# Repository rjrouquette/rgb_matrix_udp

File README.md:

# RGB Matrix Panel Driver using Raspberry Pi
Uses UDP protocol and a custom adapter board to drive RGB Panels.

The custom driver board eliminates flickering under high CPU load by utilizing the DPI interface to generate the output signals independent of the CPU.  This prevents heavy CPU load and interrupts from causing the panel brightness to flicker.  The DPI interfaces provides a 24-bit parallel interface with pixel clock, HSYNC, and VSYNC signals.  The 24-bit width allows for driving 4 chains of LED panels.

The UDP server and clients synchornize multiple Raspberry Pis to support both larger aggregate arrays and duplication of video feeds.  The server and clients must be synchronized to the same master clock using either chrony or ntpd.

This project references https://github.com/hzeller/rpi-rgb-led-matrix

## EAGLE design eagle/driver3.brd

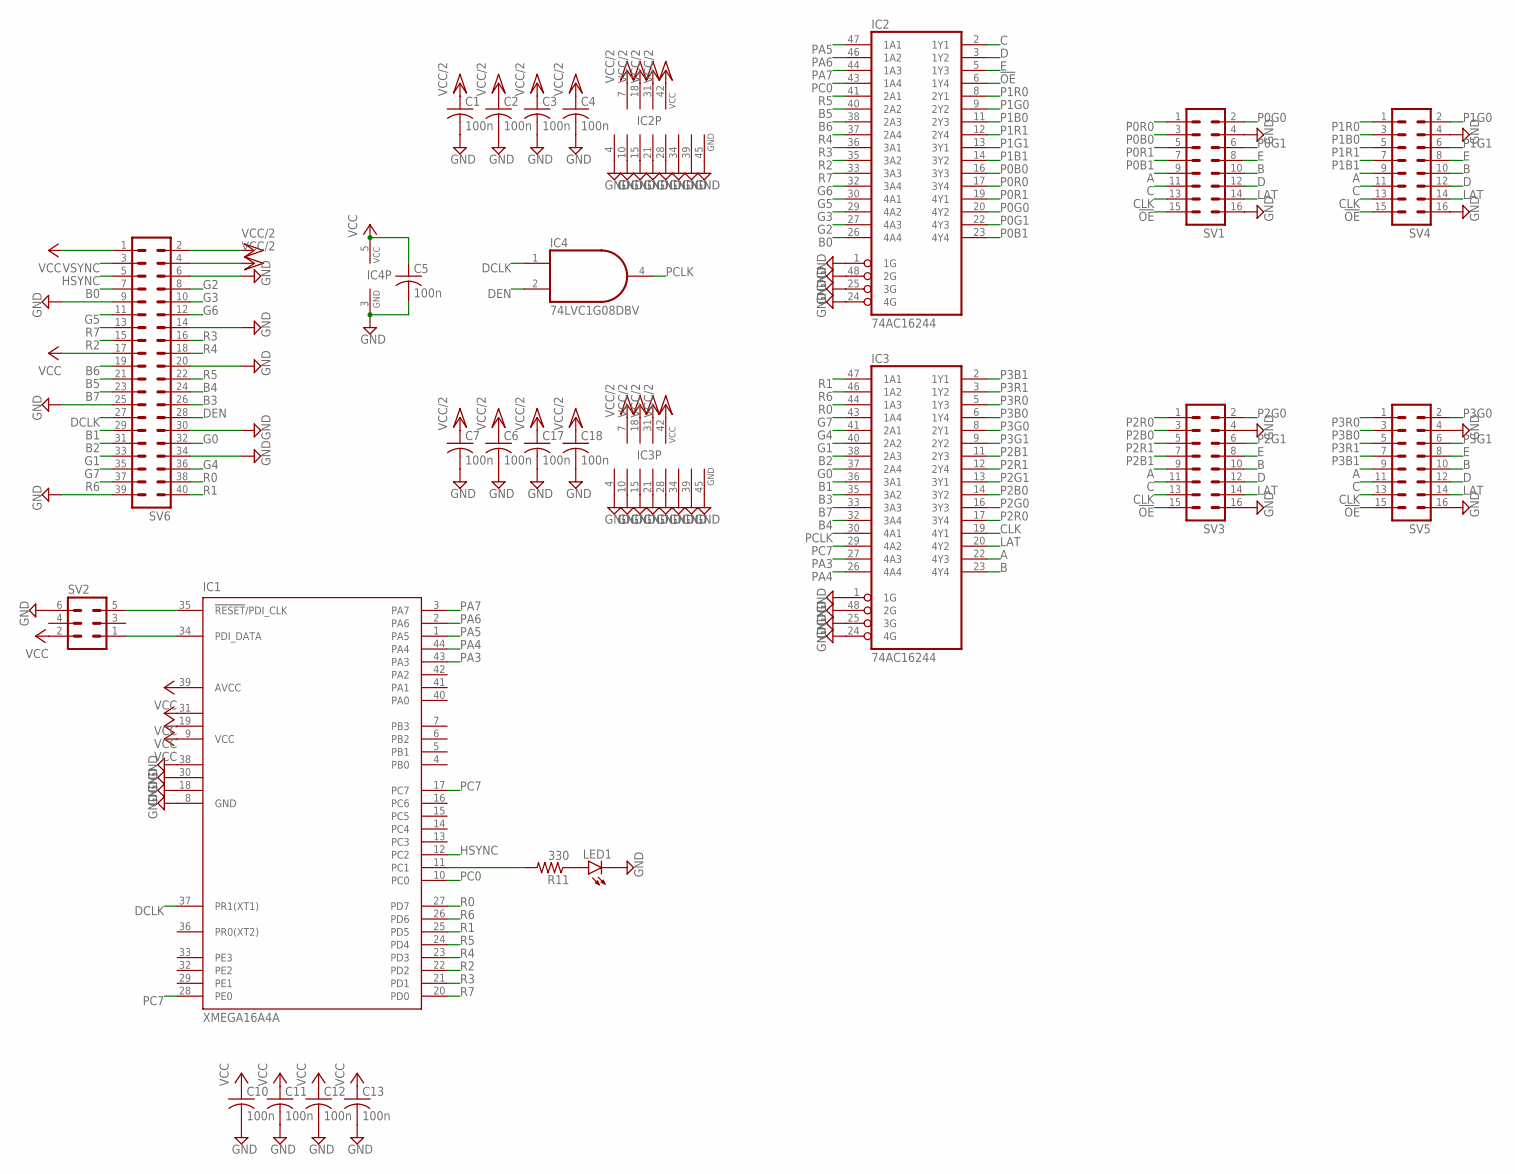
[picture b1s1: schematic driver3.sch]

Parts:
C1, C2, C3, C4, C5, C6, C7, C10, C11, C12, C13, C17, C18: 100n; C0402
IC1: XMEGA16A4A; TQFP44
IC2, IC3: 74AC16244; SSOP48DL
IC4: 74LVC1G08DBV; SOT23-5
LED1: LEDCHIPLED_0805; CHIPLED_0805
R11: 330; R0402
SV1, SV3, SV4, SV5: MA08-2
SV2: MA03-2
SV6: MA20-2

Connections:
!OE: IC2.6 (1Y4), SV1.15, SV3.15, SV4.15, SV5.15
A: IC3.22 (4Y3), SV1.9, SV3.9, SV4.9, SV5.9
B: IC3.23 (4Y4), SV1.10, SV3.10, SV4.10, SV5.10
B0: IC2.26 (4A4), SV6.7
B1: IC3.36 (3A1), SV6.29
B2: IC3.38 (2A3), SV6.31
B3: IC3.35 (3A2), SV6.26
B4: IC3.32 (3A4), SV6.24
B5: IC2.40 (2A2), SV6.21
B6: IC2.38 (2A3), SV6.19
B7: IC3.33 (3A3), SV6.23
C: IC2.2 (1Y1), SV1.11, SV3.11, SV4.11, SV5.11
CLK: IC3.19 (4Y1), SV1.13, SV3.13, SV4.13, SV5.13
D: IC2.3 (1Y2), SV1.12, SV3.12, SV4.12, SV5.12
DCLK: IC1.37 (PR1(XT1)), IC4.1 (I0), SV6.27
DEN: IC4.2 (I1), SV6.28
E: IC2.5 (1Y3), SV1.8, SV3.8, SV4.8, SV5.8
G0: IC3.37 (2A4), SV6.32
G1: IC3.40 (2A2), SV6.33
G2: IC2.27 (4A3), SV6.8
G3: IC2.29 (4A2), SV6.10
G4: IC3.41 (2A1), SV6.36
G5: IC2.30 (4A1), SV6.11
G6: IC2.32 (3A4), SV6.12
G7: IC3.43 (1A4), SV6.35
GND: C1.2, C2.2, C3.2, C4.2, C5.2, C6.2, C7.2, C10.2, C11.2, C12.2, C13.2, C17.2, C18.2, IC1.8 (GND), IC1.18 (GND1), IC1.30 (GND2), IC1.38 (GND3), IC2.1 (1G), IC2.4 (GND), IC2.10 (GND), IC2.15 (GND), IC2.21 (GND), IC2.24 (4G), IC2.25 (3G), IC2.28 (GND), IC2.34 (GND), IC2.39 (GND), IC2.45 (GND), IC2.48 (2G), IC3.1 (1G), IC3.4 (GND), IC3.10 (GND), IC3.15 (GND), IC3.21 (GND), IC3.24 (4G), IC3.25 (3G), IC3.28 (GND), IC3.34 (GND), IC3.39 (GND), IC3.45 (GND), IC3.48 (2G), IC4.3 (GND), LED1.C, SV1.4, SV1.16, SV2.6, SV3.4, SV3.16, SV4.4, SV4.16, SV5.4, SV5.16, SV6.6, SV6.9, SV6.14, SV6.20, SV6.25, SV6.30, SV6.34, SV6.39
HSYNC: IC1.12 (PC2), SV6.5
LAT: IC3.20 (4Y2), SV1.14, SV3.14, SV4.14, SV5.14
unnamed: IC1.11 (PC1), R11.2
unnamed: IC1.34 (PDI_DATA), SV2.1
unnamed: IC1.35 (!RESET!/PDI_CLK), SV2.5
unnamed: LED1.A, R11.1
P0B0: IC2.16 (3Y3), SV1.3
P0B1: IC2.23 (4Y4), SV1.7
P0G0: IC2.20 (4Y2), SV1.2
P0G1: IC2.22 (4Y3), SV1.6
P0R0: IC2.17 (3Y4), SV1.1
P0R1: IC2.19 (4Y1), SV1.5
P1B0: IC2.11 (2Y3), SV4.3
P1B1: IC2.14 (3Y2), SV4.7
P1G0: IC2.9 (2Y2), SV4.2
P1G1: IC2.13 (3Y1), SV4.6
P1R0: IC2.8 (2Y1), SV4.1
P1R1: IC2.12 (2Y4), SV4.5
P2B0: IC3.14 (3Y2), SV3.3
P2B1: IC3.11 (2Y3), SV3.7
P2G0: IC3.16 (3Y3), SV3.2
P2G1: IC3.13 (3Y1), SV3.6
P2R0: IC3.17 (3Y4), SV3.1
P2R1: IC3.12 (2Y4), SV3.5
P3B0: IC3.6 (1Y4), SV5.3
P3B1: IC3.2 (1Y1), SV5.7
P3G0: IC3.8 (2Y1), SV5.2
P3G1: IC3.9 (2Y2), SV5.6
P3R0: IC3.5 (1Y3), SV5.1
P3R1: IC3.3 (1Y2), SV5.5
PA3: IC1.43 (PA3), IC3.27 (4A3)
PA4: IC1.44 (PA4), IC3.26 (4A4)
PA5: IC1.1 (PA5), IC2.47 (1A1)
PA6: IC1.2 (PA6), IC2.46 (1A2)
PA7: IC1.3 (PA7), IC2.44 (1A3)
PC0: IC1.10 (PC0), IC2.43 (1A4)
PC7: IC1.17 (PC7), IC1.28 (PE0), IC3.29 (4A2)
PCLK: IC3.30 (4A1), IC4.4 (O)
R0: IC1.27 (PD7), IC3.44 (1A3), SV6.38
R1: IC1.25 (PD5), IC3.47 (1A1), SV6.40
R2: IC1.22 (PD2), IC2.35 (3A2), SV6.15
R3: IC1.21 (PD1), IC2.36 (3A1), SV6.16
R4: IC1.23 (PD3), IC2.37 (2A4), SV6.18
R5: IC1.24 (PD4), IC2.41 (2A1), SV6.22
R6: IC1.26 (PD6), IC3.46 (1A2), SV6.37
R7: IC1.20 (PD0), IC2.33 (3A3), SV6.13
VCC: C5.1, C10.1, C11.1, C12.1, C13.1, IC1.9 (VCC), IC1.19 (VCC1), IC1.31 (VCC2), IC1.39 (AVCC), IC4.5 (VCC), SV2.2, SV6.1, SV6.17
VCC/2: C1.1, C2.1, C3.1, C4.1, C6.1, C7.1, C17.1, C18.1, IC2.7 (VCC), IC2.18 (VCC), IC2.31 (VCC), IC2.42 (VCC), IC3.7 (VCC), IC3.18 (VCC), IC3.31 (VCC), IC3.42 (VCC), SV6.2, SV6.4
VSYNC: SV6.3

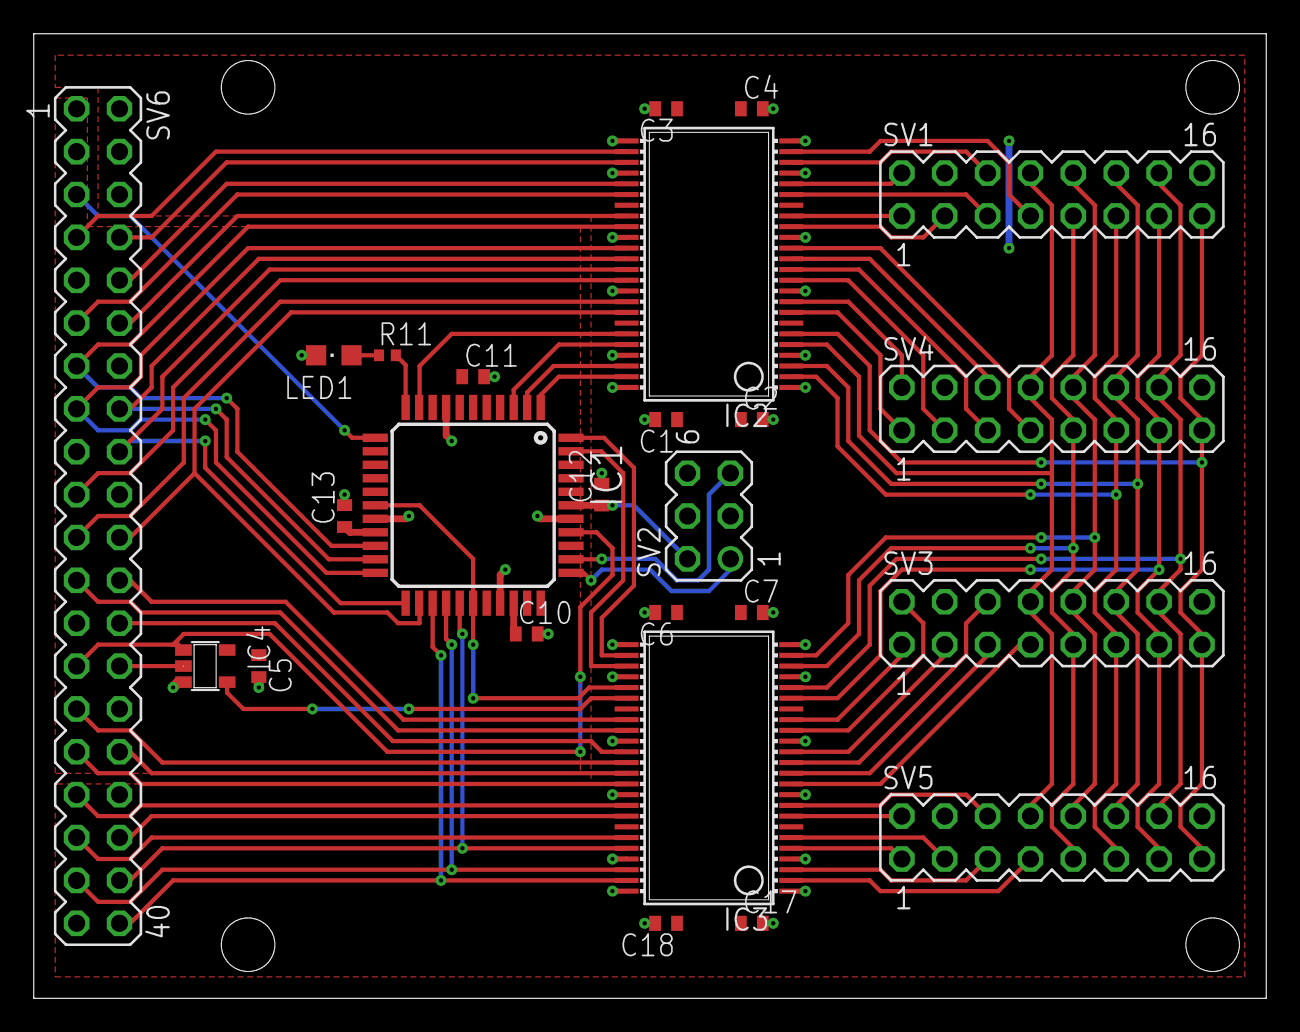
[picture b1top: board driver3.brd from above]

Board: 2 copper layers, 73.0 x 57.1 mm, 25 parts (0 on the bottom side), 74 nets.

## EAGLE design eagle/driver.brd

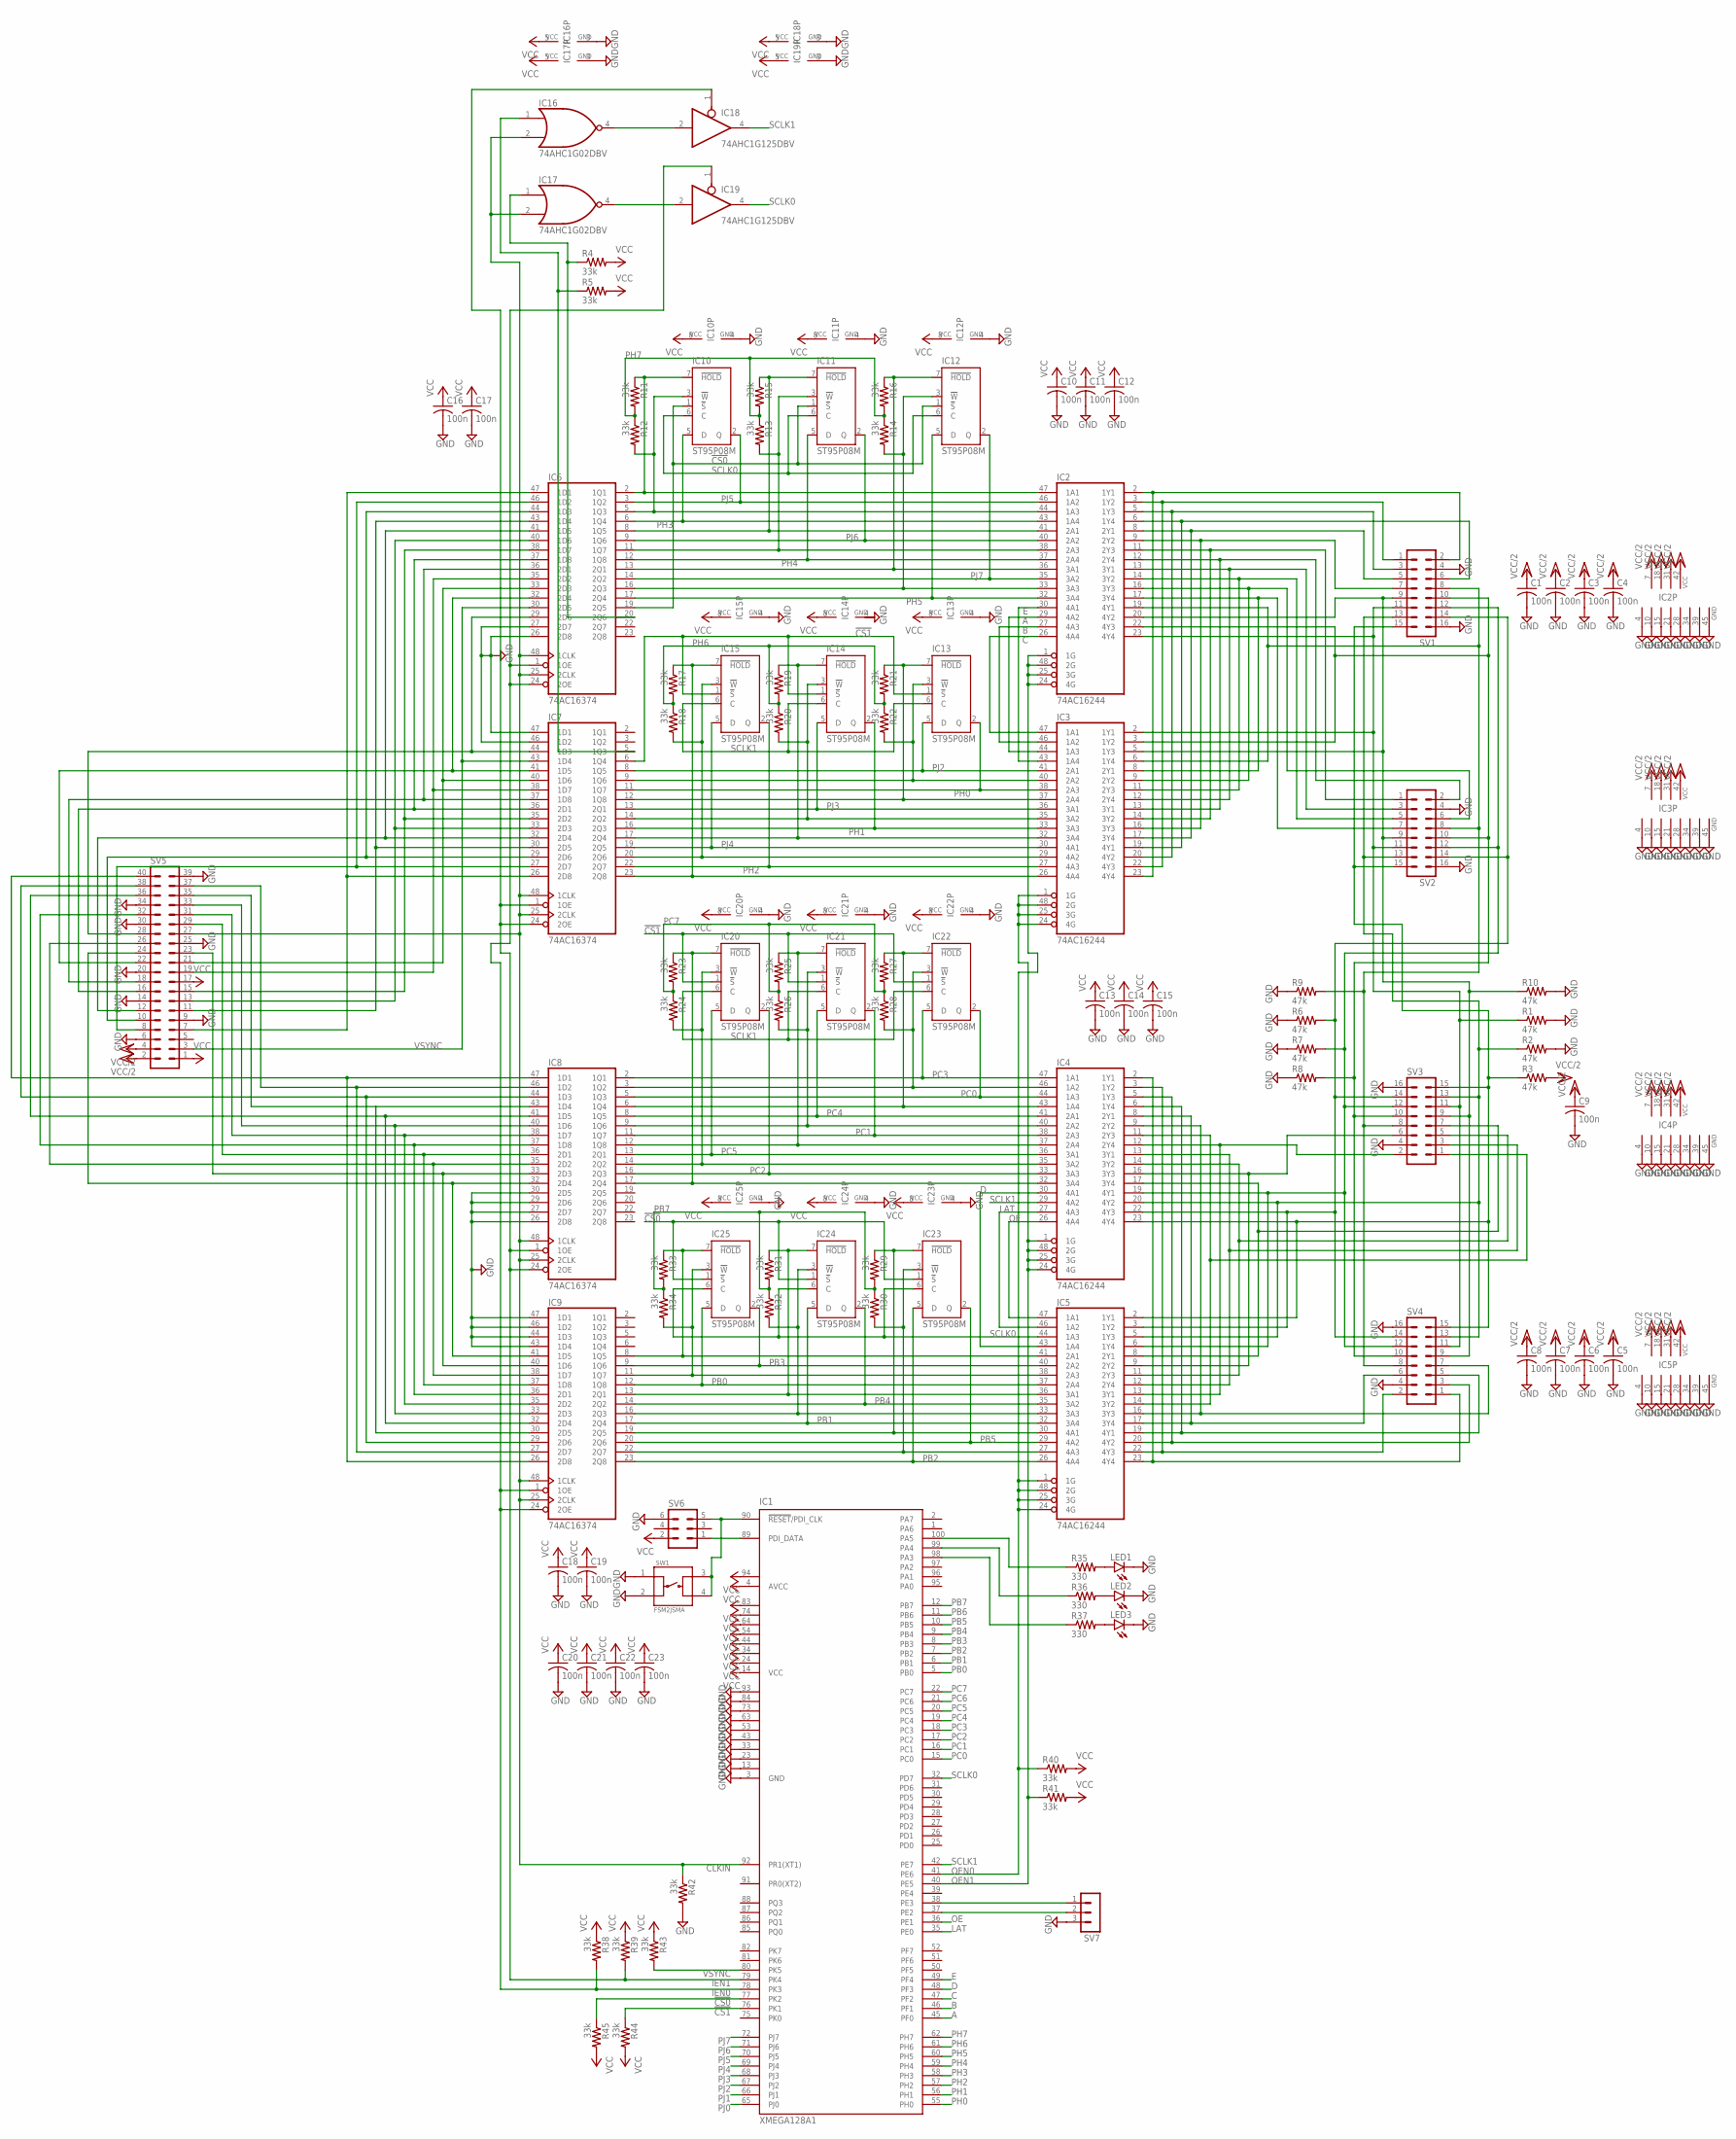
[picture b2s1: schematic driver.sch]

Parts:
C1, C2, C3, C4, C5, C6, C7, C8, C9, C10, C11, C12, C13, C14, C15, C16, C17, C18, C19, C20, C21, C22, C23: 100n; C0402
IC1: XMEGA128A1; TQFP100
IC2, IC3, IC4, IC5: 74AC16244; SSOP48DL
IC6, IC7, IC8, IC9: 74AC16374; SSOP48DL
IC10, IC11, IC12, IC13, IC14, IC15, IC20, IC21, IC22, IC23, IC24, IC25: ST95P08M; SO08
IC16, IC17: 74AHC1G02DBV; SOT23-5
IC18, IC19: 74AHC1G125DBV; SOT23-5
LED1, LED2, LED3: LEDCHIPLED_0805; CHIPLED_0805
R1, R2, R3, R6, R7, R8, R9, R10: 47k; R0402
R4, R5, R11, R12, R13, R14, R15, R16, R17, R18, R19, R20, R21, R22, R23, R24, R25, R26, R27, R28, R29, R30, R31, R32, R33, R34, R38, R39, R40, R41, R42, R43, R44, R45: 33k; R0402
R35, R36, R37: 330; R0402
SV1, SV2, SV3, SV4: MA08-2
SV5: MA20-2
SV6: MA03-2
SV7: MA03-1
SW1: FSM2JSMA

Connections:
!CS0: IC1.77 (PK2), IC6.19 (2Q5), IC10.1 (!S), IC11.1 (!S), IC12.1 (!S), IC23.1 (!S), IC24.1 (!S), IC25.1 (!S), R45.1
!CS1: IC1.76 (PK1), IC7.6 (1Q4), IC13.1 (!S), IC14.1 (!S), IC15.1 (!S), IC20.1 (!S), IC21.1 (!S), IC22.1 (!S), R44.1
A: IC1.45 (PF0), IC2.29 (4A2), IC3.44 (1A3)
B: IC1.46 (PF1), IC2.27 (4A3), IC3.46 (1A2)
C: IC1.47 (PF2), IC2.26 (4A4), IC3.47 (1A1)
CLKIN: IC1.92 (PR1(XT1)), IC6.25 (2CLK), IC6.48 (1CLK), IC7.25 (2CLK), IC7.48 (1CLK), IC8.25 (2CLK), IC8.48 (1CLK), IC9.25 (2CLK), IC9.48 (1CLK), IC16.2 (I1), IC17.2 (I1), R42.1, SV5.27
D: IC1.48 (PF3), IC4.30 (4A1), IC5.43 (1A4)
E: IC1.49 (PF4), IC2.30 (4A1), IC3.43 (1A4)
GND: C1.2, C2.2, C3.2, C4.2, C5.2, C6.2, C7.2, C8.2, C9.2, C10.2, C11.2, C12.2, C13.2, C14.2, C15.2, C16.2, C17.2, C18.2, C19.2, C20.2, C21.2, C22.2, C23.2, IC1.3 (GND), IC1.13 (GND1), IC1.23 (GND2), IC1.33 (GND3), IC1.43 (GND4), IC1.53 (GND5), IC1.63 (GND6), IC1.73 (GND7), IC1.84 (GND8), IC1.93 (GND9), IC2.4 (GND), IC2.10 (GND), IC2.15 (GND), IC2.21 (GND), IC2.28 (GND), IC2.34 (GND), IC2.39 (GND), IC2.45 (GND), IC3.4 (GND), IC3.10 (GND), IC3.15 (GND), IC3.21 (GND), IC3.28 (GND), IC3.34 (GND), IC3.39 (GND), IC3.45 (GND), IC4.4 (GND), IC4.10 (GND), IC4.15 (GND), IC4.21 (GND), IC4.28 (GND), IC4.34 (GND), IC4.39 (GND), IC4.45 (GND), IC5.4 (GND), IC5.10 (GND), IC5.15 (GND), IC5.21 (GND), IC5.28 (GND), IC5.34 (GND), IC5.39 (GND), IC5.45 (GND), IC6.4 (GND), IC6.10 (GND), IC6.15 (GND), IC6.21 (GND), IC6.26 (2D8), IC6.27 (2D7), IC6.28 (GND), IC6.34 (GND), IC6.39 (GND), IC6.45 (GND), IC7.4 (GND), IC7.10 (GND), IC7.15 (GND), IC7.21 (GND), IC7.28 (GND), IC7.34 (GND), IC7.39 (GND), IC7.45 (GND), IC7.46 (1D2), IC7.47 (1D1), IC8.4 (GND), IC8.10 (GND), IC8.15 (GND), IC8.21 (GND), IC8.26 (2D8), IC8.27 (2D7), IC8.28 (GND), IC8.29 (2D6), IC8.30 (2D5), IC8.34 (GND), IC8.39 (GND), IC8.45 (GND), IC9.4 (GND), IC9.10 (GND), IC9.15 (GND), IC9.21 (GND), IC9.28 (GND), IC9.34 (GND), IC9.39 (GND), IC9.43 (1D4), IC9.44 (1D3), IC9.45 (GND), IC9.46 (1D2), IC9.47 (1D1), IC10.4 (GND), IC11.4 (GND), IC12.4 (GND), IC13.4 (GND), IC14.4 (GND), IC15.4 (GND), IC16.3 (GND), IC17.3 (GND), IC18.3 (GND), IC19.3 (GND), IC20.4 (GND), IC21.4 (GND), IC22.4 (GND)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
IEN0: IC1.78 (PK3), IC6.1 (1OE), IC6.24 (2OE), IC9.1 (1OE), IC9.24 (2OE), IC19.1 (OE), R38.2
IEN1: IC1.79 (PK4), IC7.1 (1OE), IC7.24 (2OE), IC8.1 (1OE), IC8.24 (2OE), IC18.1 (OE), R39.2
LAT: IC1.35 (PE0), IC4.27 (4A3), IC5.46 (1A2)
unnamed: IC2.2 (1Y1), IC3.23 (4Y4), SV1.2
unnamed: IC2.3 (1Y2), IC3.22 (4Y3), SV1.1
unnamed: IC2.6 (1Y4), IC3.19 (4Y1), SV1.6
unnamed: IC2.5 (1Y3), IC3.20 (4Y2), SV1.3
unnamed: IC2.8 (2Y1), IC3.17 (3Y4), SV1.5
unnamed: IC2.9 (2Y2), IC3.16 (3Y3), SV1.7
unnamed: IC2.12 (2Y4), IC3.13 (3Y1), SV2.2
unnamed: IC2.14 (3Y2), IC3.11 (2Y3), SV2.5
unnamed: IC2.13 (3Y1), IC3.12 (2Y4), SV2.3
unnamed: IC2.16 (3Y3), IC3.9 (2Y2), SV2.6
unnamed: IC2.19 (4Y1), IC3.6 (1Y4), R9.2, SV1.8, SV2.8, SV3.8, SV4.8
unnamed: IC2.20 (4Y2), IC3.5 (1Y3), R10.1, SV1.9, SV2.9, SV3.9, SV4.9
unnamed: IC2.11 (2Y3), IC3.14 (3Y2), SV2.1
unnamed: IC2.23 (4Y4), IC3.2 (1Y1), R1.1, SV1.11, SV2.11, SV3.11, SV4.11
unnamed: IC2.22 (4Y3), IC3.3 (1Y2), R8.2, SV1.10, SV2.10, SV3.10, SV4.10
unnamed: IC4.19 (4Y1), IC5.6 (1Y4), R7.2, SV1.12, SV2.12, SV3.12, SV4.12
unnamed: IC2.17 (3Y4), IC3.8 (2Y1), SV2.7
unnamed: IC4.20 (4Y2), IC5.5 (1Y3), R2.1, SV1.13, SV2.13, SV3.13, SV4.13
unnamed: IC4.23 (4Y4), IC5.2 (1Y1), R3.1, SV1.15, SV2.15, SV3.15, SV4.15
unnamed: IC4.3 (1Y2), IC5.22 (4Y3), SV4.2
unnamed: IC4.2 (1Y1), IC5.23 (4Y4), SV4.1
unnamed: IC4.5 (1Y3), IC5.20 (4Y2), SV4.3
unnamed: IC4.6 (1Y4), IC5.19 (4Y1), SV4.5
unnamed: IC4.8 (2Y1), IC5.17 (3Y4), SV4.6
unnamed: IC4.22 (4Y3), IC5.3 (1Y2), R6.2, SV1.14, SV2.14, SV3.14, SV4.14
unnamed: IC4.9 (2Y2), IC5.16 (3Y3), SV4.7
unnamed: IC2.47 (1A1), IC6.2 (1Q1), IC10.7 (!HOLD), R11.1
unnamed: IC6.32 (2D4), IC7.41 (1D5), SV5.22
unnamed: IC2.44 (1A3), IC6.5 (1Q3), IC10.3 (!W), R12.2
unnamed: IC4.11 (2Y3), IC5.14 (3Y2), SV3.1
unnamed: IC4.12 (2Y4), IC5.13 (3Y1), SV3.2
unnamed: IC6.33 (2D3), IC7.40 (1D6), SV5.21
unnamed: IC2.41 (2A1), IC6.8 (1Q5), IC11.7 (!HOLD), R15.1
unnamed: IC4.13 (3Y1), IC5.12 (2Y4), SV3.3
unnamed: IC4.14 (3Y2), IC5.11 (2Y3), SV3.5
unnamed: IC4.16 (3Y3), IC5.9 (2Y2), SV3.6
unnamed: IC4.17 (3Y4), IC5.8 (2Y1), SV3.7
unnamed: IC6.35 (2D2), IC7.38 (1D7), SV5.19
unnamed: IC2.38 (2A3), IC6.11 (1Q7), IC11.3 (!W), R13.2
unnamed: IC16.4 (O), IC18.2 (I)
unnamed: IC2.36 (3A1), IC6.13 (2Q1), IC12.7 (!HOLD), R16.1
unnamed: IC6.36 (2D1), IC7.37 (1D8), SV5.18
unnamed: IC2.33 (3A3), IC6.16 (2Q3), IC12.3 (!W), R14.2
unnamed: IC17.4 (O), IC19.2 (I)
unnamed: IC3.26 (4A4), IC7.23 (2Q8), IC15.7 (!HOLD), R17.1
unnamed: IC3.29 (4A2), IC7.20 (2Q6), IC15.3 (!W), R18.2
unnamed: IC6.37 (1D8), IC7.36 (2D1), SV5.16
unnamed: IC3.32 (3A4), IC7.17 (2Q4), IC14.7 (!HOLD), R19.1
unnamed: IC6.38 (1D7), IC7.35 (2D2), SV5.15
unnamed: IC3.35 (3A2), IC7.14 (2Q2), IC14.3 (!W), R20.2
unnamed: IC6.40 (1D6), IC7.33 (2D3), SV5.13
unnamed: IC3.37 (2A4), IC7.12 (1Q8), IC13.7 (!HOLD), R21.1
unnamed: IC3.40 (2A2), IC7.9 (1Q6), IC13.3 (!W), R22.2
unnamed: IC6.41 (1D5), IC7.32 (2D4), SV5.12
unnamed: IC6.43 (1D4), IC7.30 (2D5), SV5.11
unnamed: IC6.44 (1D3), IC7.29 (2D6), SV5.10
unnamed: IC6.46 (1D2), IC7.27 (2D7), SV5.8
unnamed: IC6.47 (1D1), IC7.26 (2D8), SV5.7
unnamed: IC1.90 (!RESET!/PDI_CLK), SV6.5, SW1.3, SW1.4
unnamed: IC4.46 (1A2), IC8.3 (1Q2), IC22.3 (!W), R28.2
unnamed: IC4.43 (1A4), IC8.6 (1Q4), IC22.7 (!HOLD), R27.1
unnamed: LED3.A, R37.2
unnamed: LED2.A, R36.2
unnamed: IC4.40 (2A2), IC8.9 (1Q6), IC21.3 (!W), R26.2
unnamed: LED1.A, R35.2
unnamed: IC4.37 (2A4), IC8.12 (1Q8), IC21.7 (!HOLD), R25.1
unnamed: IC1.100 (PA5), R35.1
unnamed: IC4.35 (3A2), IC8.14 (2Q2), IC20.3 (!W), R24.2
unnamed: IC1.99 (PA4), R36.1
unnamed: IC4.32 (3A4), IC8.17 (2Q4), IC20.7 (!HOLD), R23.1
unnamed: IC1.98 (PA3), R37.1
unnamed: IC5.27 (4A3), IC9.22 (2Q7), IC23.3 (!W), R30.2
unnamed: IC5.30 (4A1), IC9.19 (2Q5), IC23.7 (!HOLD), R29.1
unnamed: IC5.33 (3A3), IC9.16 (2Q3), IC24.3 (!W), R32.2
unnamed: IC5.36 (3A1), IC9.13 (2Q1), IC24.7 (!HOLD), R31.1
unnamed: IC5.38 (2A3), IC9.11 (1Q7), IC25.3 (!W), R34.2
unnamed: IC5.41 (2A1), IC9.8 (1Q5), IC25.7 (!HOLD), R33.1
unnamed: IC1.89 (PDI_DATA), SV6.1
unnamed: IC1.38 (PE3), SV7.1
unnamed: IC1.37 (PE2), SV7.2
unnamed: IC8.32 (2D4), IC9.41 (1D5), SV5.24
unnamed: IC6.29 (2D6), IC7.44 (1D3), SV5.28
unnamed: IC8.33 (2D3), IC9.40 (1D6), SV5.23
unnamed: IC8.35 (2D2), IC9.38 (1D7), SV5.26
unnamed: IC8.36 (2D1), IC9.37 (1D8), SV5.29
unnamed: IC8.37 (1D8), IC9.36 (2D1), SV5.32
unnamed: IC8.38 (1D7), IC9.35 (2D2), SV5.31
unnamed: IC8.40 (1D6), IC9.33 (2D3), SV5.33
unnamed: IC8.43 (1D4), IC9.30 (2D5), SV5.35
unnamed: IC8.44 (1D3), IC9.29 (2D6), SV5.38
unnamed: IC6.20 (2Q6), IC17.1 (I0), R4.1
unnamed: IC8.46 (1D2), IC9.27 (2D7), SV5.37
unnamed: IC8.47 (1D1), IC9.26 (2D8), SV5.40
unnamed: IC7.5 (1Q3), IC16.1 (I0), R5.1
unnamed: IC8.41 (1D5), IC9.32 (2D4), SV5.36
OE: IC1.36 (PE1), IC4.26 (4A4), IC5.47 (1A1)
OEN0: IC1.41 (PE6), IC2.1 (1G), IC2.24 (4G), IC2.25 (3G), IC2.48 (2G), IC5.1 (1G), IC5.24 (4G), IC5.25 (3G), IC5.48 (2G), R40.1
OEN1: IC1.40 (PE5), IC3.1 (1G), IC3.24 (4G), IC3.25 (3G), IC3.48 (2G), IC4.1 (1G), IC4.24 (4G), IC4.25 (3G), IC4.48 (2G), R41.1
PB0: IC1.5 (PB0), IC5.37 (2A4), IC9.12 (1Q8), IC25.5 (D)
PB1: IC1.6 (PB1), IC5.32 (3A4), IC9.17 (2Q4), IC24.5 (D)
PB2: IC1.7 (PB2), IC5.26 (4A4), IC9.23 (2Q8), IC23.5 (D)
PB3: IC1.8 (PB3), IC5.40 (2A2), IC9.9 (1Q6), IC25.2 (Q)
PB4: IC1.9 (PB4), IC5.35 (3A2), IC9.14 (2Q2), IC24.2 (Q)
PB5: IC1.10 (PB5), IC5.29 (4A2), IC9.20 (2Q6), IC23.2 (Q)
PB6: IC1.11 (PB6)
PB7: IC1.12 (PB7), R29.2, R30.1, R31.2, R32.1, R33.2, R34.1
PC0: IC1.15 (PC0), IC4.44 (1A3), IC8.5 (1Q3), IC22.2 (Q)
PC1: IC1.16 (PC1), IC4.38 (2A3), IC8.11 (1Q7), IC21.2 (Q)
PC2: IC1.17 (PC2), IC4.33 (3A3), IC8.16 (2Q3), IC20.2 (Q)
PC3: IC1.18 (PC3), IC4.47 (1A1), IC8.2 (1Q1), IC22.5 (D)
PC4: IC1.19 (PC4), IC4.41 (2A1), IC8.8 (1Q5), IC21.5 (D)
PC5: IC1.20 (PC5), IC4.36 (3A1), IC8.13 (2Q1), IC20.5 (D)
PC6: IC1.21 (PC6)
PC7: IC1.22 (PC7), R23.2, R24.1, R25.2, R26.1, R27.2, R28.1
PH0: IC1.55 (PH0), IC3.38 (2A3), IC7.11 (1Q7), IC13.2 (Q)
PH1: IC1.56 (PH1), IC3.33 (3A3), IC7.16 (2Q3), IC14.2 (Q)
PH2: IC1.57 (PH2), IC3.27 (4A3), IC7.22 (2Q7), IC15.2 (Q)
PH3: IC1.58 (PH3), IC2.43 (1A4), IC6.6 (1Q4), IC10.5 (D)
PH4: IC1.59 (PH4), IC2.37 (2A4), IC6.12 (1Q8), IC11.5 (D)
PH5: IC1.60 (PH5), IC2.32 (3A4), IC6.17 (2Q4), IC12.5 (D)
PH6: IC1.61 (PH6), R17.2, R18.1, R19.2, R20.1, R21.2, R22.1
PH7: IC1.62 (PH7), R11.2, R12.1, R13.1, R14.1, R15.2, R16.2
PJ0: IC1.65 (PJ0)
PJ1: IC1.66 (PJ1)
PJ2: IC1.67 (PJ2), IC3.41 (2A1), IC7.8 (1Q5), IC13.5 (D)
PJ3: IC1.68 (PJ3), IC3.36 (3A1), IC7.13 (2Q1), IC14.5 (D)
PJ4: IC1.69 (PJ4), IC3.30 (4A1), IC7.19 (2Q5), IC15.5 (D)
PJ5: IC1.70 (PJ5), IC2.46 (1A2), IC6.3 (1Q2), IC10.2 (Q)
PJ6: IC1.71 (PJ6), IC2.40 (2A2), IC6.9 (1Q6), IC11.2 (Q)
PJ7: IC1.72 (PJ7), IC2.35 (3A2), IC6.14 (2Q2), IC12.2 (Q)
SCLK0: IC1.32 (PD7), IC5.44 (1A3), IC10.6 (C), IC11.6 (C), IC12.6 (C), IC19.4 (O), IC23.6 (C), IC24.6 (C), IC25.6 (C)
SCLK1: IC1.42 (PE7), IC4.29 (4A2), IC13.6 (C), IC14.6 (C), IC15.6 (C), IC18.4 (O), IC20.6 (C), IC21.6 (C), IC22.6 (C)
VCC: C10.1, C11.1, C12.1, C13.1, C14.1, C15.1, C16.1, C17.1, C18.1, C19.1, C20.1, C21.1, C22.1, C23.1, IC1.4 (AVCC), IC1.14 (VCC), IC1.24 (VCC1), IC1.34 (VCC2), IC1.44 (VCC3), IC1.54 (VCC4), IC1.64 (VCC5), IC1.74 (VCC6), IC1.83 (VCC7), IC1.94 (AVCC1), IC6.7 (VCC), IC6.18 (VCC), IC6.31 (VCC), IC6.42 (VCC), IC7.7 (VCC), IC7.18 (VCC), IC7.31 (VCC), IC7.42 (VCC), IC8.7 (VCC), IC8.18 (VCC), IC8.31 (VCC), IC8.42 (VCC), IC9.7 (VCC), IC9.18 (VCC), IC9.31 (VCC), IC9.42 (VCC), IC10.8 (VCC), IC11.8 (VCC), IC12.8 (VCC), IC13.8 (VCC), IC14.8 (VCC), IC15.8 (VCC), IC16.5 (VCC), IC17.5 (VCC), IC18.5 (VCC), IC19.5 (VCC), IC20.8 (VCC), IC21.8 (VCC), IC22.8 (VCC), IC23.8 (VCC), IC24.8 (VCC), IC25.8 (VCC), R4.2, R5.2, R38.1, R39.1, R40.2, R41.2, R43.1, R44.2, R45.2, SV5.1, SV5.17, SV6.2
VCC/2: C1.1, C2.1, C3.1, C4.1, C5.1, C6.1, C7.1, C8.1, C9.1, IC2.7 (VCC), IC2.18 (VCC), IC2.31 (VCC), IC2.42 (VCC), IC3.7 (VCC), IC3.18 (VCC), IC3.31 (VCC), IC3.42 (VCC), IC4.7 (VCC), IC4.18 (VCC), IC4.31 (VCC), IC4.42 (VCC), IC5.7 (VCC), IC5.18 (VCC), IC5.31 (VCC), IC5.42 (VCC), R3.2, SV5.2, SV5.4
VSYNC: IC1.80 (PK5), IC6.30 (2D5), IC7.43 (1D4), R43.2, SV5.3

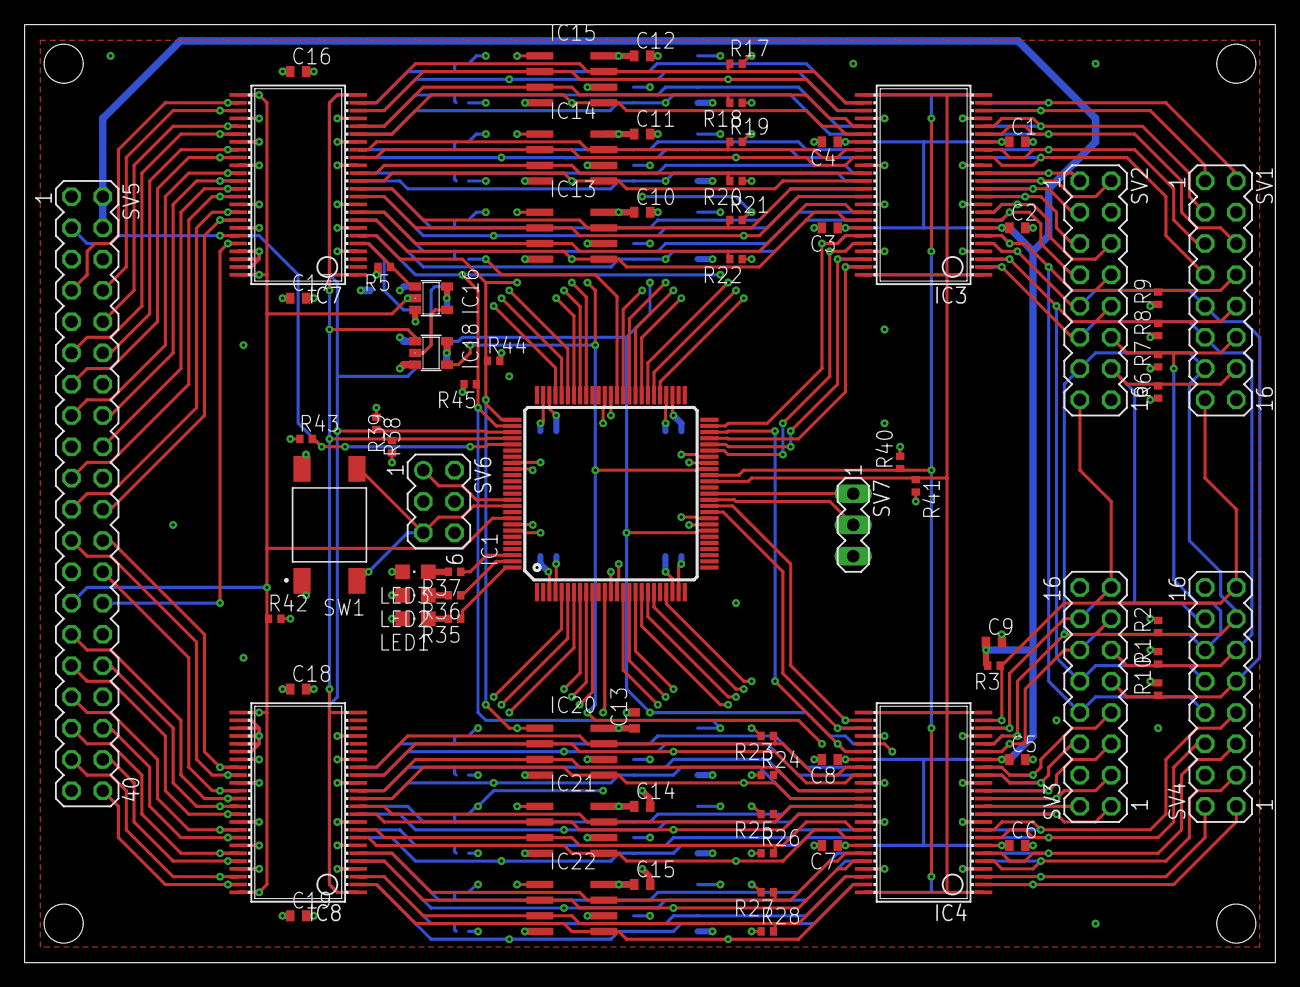
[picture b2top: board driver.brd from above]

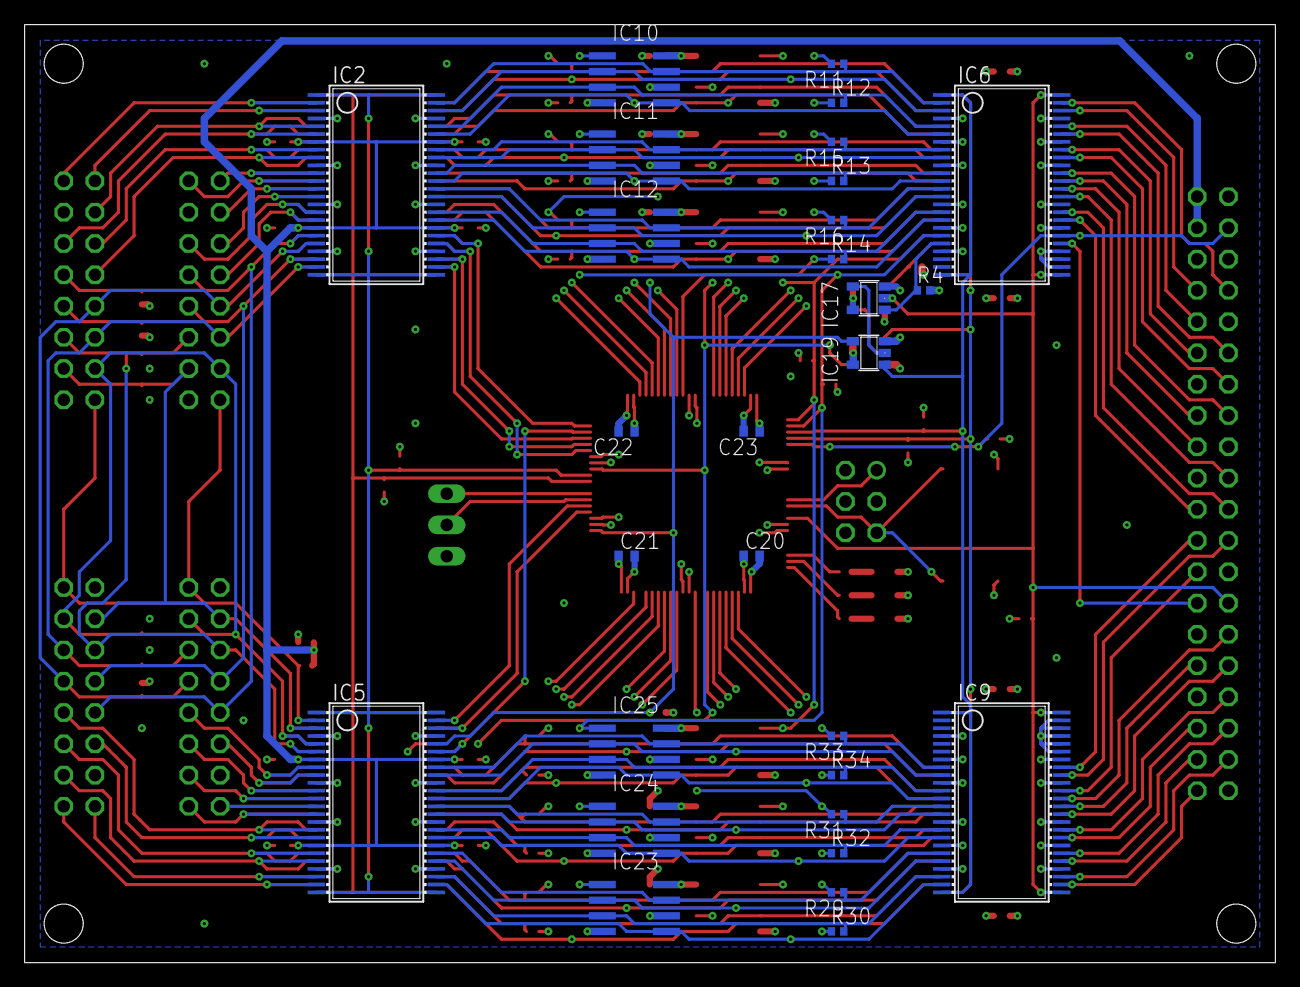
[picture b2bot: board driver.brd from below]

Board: 4 copper layers, 101.6 x 76.2 mm, 104 parts (29 on the bottom side), 143 nets.

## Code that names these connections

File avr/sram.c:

//
// Created by robert on 9/18/19.
//

#include "sram.h"

void initSRAM() {
    // reset SRAM bus mode
    // set chip selects
    csOn0();
    csOn1();
    // set upper command bits (PH6, PH7, PC7, PB7)
    PORTH.DIRSET = 0xc0u;
    PORTC.DIRSET = 0x80u;
    PORTB.DIRSET = 0x80u;
    PORTH.OUTSET = 0xc0u;
    PORTC.OUTSET = 0x80u;
    PORTB.OUTSET = 0x80u;
    // raise lower command bits
    PORTH.DIRSET = BANK0H_MASK | BANK1H_MASK;
    PORTJ.DIRSET = BANK0J_MASK | BANK1J_MASK;
    PORTC.DIRSET = BANK1C_MASK;
    PORTB.DIRSET = BANK0B_MASK;
    PORTH.OUTSET = BANK0H_MASK | BANK1H_MASK;
    PORTJ.OUTSET = BANK0J_MASK | BANK1J_MASK;
    PORTC.OUTSET = BANK1C_MASK;
    PORTB.OUTSET = BANK0B_MASK;

    // wait for data pins to stabilize
    for(uint16_t cnt = 0; cnt < 0xffffu; cnt++) asm("nop\nnop\nnop\nnop");

    // clock data 8 times to guarantee bus mode reset
    pulseClk0(); pulseClk1();
    pulseClk0(); pulseClk1();
    pulseClk0(); pulseClk1();
    pulseClk0(); pulseClk1();
    pulseClk0(); pulseClk1();
    pulseClk0(); pulseClk1();
    pulseClk0(); pulseClk1();
    pulseClk0(); pulseClk1();
    // clear chip selects
    csOff0();
    csOff1();

    // set SO bits as high impedance
    PORTH.DIRCLR = 0x07u; // PH0 - PH2
    PORTJ.DIRCLR = 0xe0u; // PJ5 - PJ7
    PORTC.DIRCLR = 0x07u; // PC0 - PC2
    PORTB.DIRCLR = 0x38u; // PB3 - PB5

    // set SRAM bus mode to QPI
    // set chip selects
    csOn0();
    csOn1();
    // clear lower command bits
    PORTH.OUTCLR = BANK0H_MASK | BANK1H_MASK;
    PORTJ.OUTCLR = BANK0J_MASK | BANK1J_MASK;
    PORTC.OUTCLR = BANK1C_MASK;
    PORTB.OUTCLR = BANK0B_MASK;
    pulseClk0(); pulseClk1();
    pulseClk0(); pulseClk1();
    // set lower command bits
    PORTH.OUTSET = BANK0H_MASK | BANK1H_MASK;
    PORTJ.OUTSET = BANK0J_MASK | BANK1J_MASK;
    PORTC.OUTSET = BANK1C_MASK;
    PORTB.OUTSET = BANK0B_MASK;
    pulseClk0(); pulseClk1();
    pulseClk0(); pulseClk1();
    pulseClk0(); pulseClk1();
    // clear lower command bits
    PORTH.OUTCLR = BANK0H_MASK | BANK1H_MASK;
    PORTJ.OUTCLR = BANK0J_MASK | BANK1J_MASK;
    PORTC.OUTCLR = BANK1C_MASK;
    PORTB.OUTCLR = BANK0B_MASK;
    pulseClk0(); pulseClk1();
    pulseClk0(); pulseClk1();
    pulseClk0(); pulseClk1();
    // clear chip selects
    csOff0();
    csOff1();

    // clear upper command bits
    PORTH.OUTCLR = 0xc0u;
    PORTC.OUTCLR = 0x80u;
    PORTB.OUTCLR = 0x80u;

    // wait for data pins to stabilize
    for(uint16_t cnt = 0; cnt < 0xffffu; cnt++) asm("nop\nnop\nnop\nnop");
}

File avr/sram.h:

//
// Created by robert on 9/18/19.
//

#ifndef RGB_MATRIX_AVR_SRAM_H
#define RGB_MATRIX_AVR_SRAM_H

#include <avr/io.h>
#include "clkout.h"

#define CS_PORT PORTK
#define CS_MASK 0x06u
#define CS_MASK_0 0x04u
#define CS_MASK_1 0x02u

inline void csOn0() {
    CS_PORT.OUTSET = CS_MASK_0;
    CS_PORT.DIRSET = CS_MASK_0;
}

inline void csOff0() {
    CS_PORT.OUTCLR = CS_MASK_0;
    CS_PORT.DIRCLR = CS_MASK_0;
}

inline void csOn1() {
    CS_PORT.OUTSET = CS_MASK_1;
    CS_PORT.DIRSET = CS_MASK_1;
}

inline void csOff1() {
    CS_PORT.OUTCLR = CS_MASK_1;
    CS_PORT.DIRCLR = CS_MASK_1;
}

inline void csOff() {
    csOff0();
    csOff1();
}

// bank 0 - PH3-PH5, PJ5-PJ7, PB0-PB5 (underside)
#define BANK0H_MASK 0x68u
#define BANK0J_MASK 0xe0u
#define BANK0B_MASK 0x3fu

inline void readBank0() {
    // set data pins as outputs
    PORTH.DIRSET = BANK0H_MASK;
    PORTJ.DIRSET = BANK0J_MASK;
    PORTB.DIRSET = BANK0B_MASK;

    // clock in READ command
    PORTH.OUTCLR = BANK0H_MASK;
    PORTJ.OUTCLR = BANK0J_MASK;
    PORTC.OUTCLR = BANK0B_MASK;
    pulseClk0();
    PORTH.OUTSET = BANK0H_MASK;
    PORTJ.OUTSET = BANK0J_MASK;
    PORTB.OUTSET = BANK0B_MASK;
    pulseClk0();

    // clock in zero as starting address
    PORTH.OUTCLR = BANK0H_MASK;
    PORTJ.OUTCLR = BANK0J_MASK;
    PORTB.OUTCLR = BANK0B_MASK;
    pulseClk0();
    pulseClk0();
    pulseClk0();
    pulseClk0();

    // set data pins as inputs
    PORTH.DIRCLR = BANK0H_MASK;
    PORTJ.DIRCLR = BANK0J_MASK;
    PORTB.DIRCLR = BANK0B_MASK;

    // dummy byte
    pulseClk0();
    pulseClk0();
}

// bank 1 - PH0-PH2, PJ2-PJ4, PC0-PC5 (topside)
#define BANK1H_MASK 0x07u
#define BANK1J_MASK 0x1cu
#define BANK1C_MASK 0x3fu

inline void readBank1() {
    // set data pins as outputs
    PORTH.DIRSET = BANK1H_MASK;
    PORTJ.DIRSET = BANK1J_MASK;
    PORTC.DIRSET = BANK1C_MASK;

    // clock in READ command
    PORTH.OUTCLR = BANK1H_MASK;
    PORTJ.OUTCLR = BANK1J_MASK;
    PORTC.OUTCLR = BANK1C_MASK;
    pulseClk1();
    PORTH.OUTSET = BANK1H_MASK;
    PORTJ.OUTSET = BANK1J_MASK;
    PORTC.OUTSET = BANK1C_MASK;
    pulseClk1();

    // clock in zero as starting address
    PORTH.OUTCLR = BANK1H_MASK;
    PORTJ.OUTCLR = BANK1J_MASK;
    PORTC.OUTCLR = BANK1C_MASK;
    pulseClk1();
    pulseClk1();
    pulseClk1();
    pulseClk1();

    // set data pins as inputs
    PORTH.DIRCLR = BANK1H_MASK;
    PORTJ.DIRCLR = BANK1J_MASK;
    PORTC.DIRCLR = BANK1C_MASK;

    // dummy byte
    pulseClk1();
    pulseClk1();
}

void initSRAM();

#endif //RGB_MATRIX_AVR_SRAM_H

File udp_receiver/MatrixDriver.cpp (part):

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// mangle header bits to match board layout
// see mapRGB above for bit offset interpretation
static const unsigned mapHeaderBits[8] = {
        027, // PD0 -> R7
        023, // PD1 -> R3
        022, // PD2 -> R2
        024, // PD3 -> R4
        025, // PD4 -> R5
        021, // PD5 -> R1
        026, // PD6 -> R6
        020  // PD7 -> R0
};

// number of scan rows for each panel type
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
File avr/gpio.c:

//
// Created by robert on 9/18/19.
//

#include "gpio.h"

void initGpio() {
    // configure LED pin (PC1)
    // disable input sensing
    LED_PORT.DIRSET = LED_MASK;
    LED_PORT.PIN1CTRL = 0x07u;

    // configure hsync input (PC2)
    HSYNC_PORT.DIRCLR = 0x04u;
    // rising edge interrupt end event
    HSYNC_PORT.PIN2CTRL = 0x01u; // rising edge
    HSYNC_PORT.INT0MASK = 0x04u; // interrupt on pin 2
    EVSYS.CH0MUX = 0x62u; // event channel 0
    // enable port interrupt
    HSYNC_PORT.INTCTRL = 0x03u; // port interrupt 0, high level

    // configure row select outputs
    // disable input sensing
    ROWSEL_PORT.DIRSET = 0xf8u;
    ROWSEL_PORT.PIN0CTRL = 0x07u;
    ROWSEL_PORT.PIN1CTRL = 0x07u;
    ROWSEL_PORT.PIN2CTRL = 0x07u;
    ROWSEL_PORT.PIN3CTRL = 0x07u;
    ROWSEL_PORT.PIN4CTRL = 0x07u;
    ROWSEL_PORT.PIN5CTRL = 0x07u;
    ROWSEL_PORT.PIN6CTRL = 0x07u;
    ROWSEL_PORT.PIN7CTRL = 0x07u;

    // init pwm timer
    PWM_TIMER.PER = 0xffffu; // maximum period
    PWM_TIMER.CCA = 0;       // start with zero width pulse
    PWM_TIMER.CTRLA = 0x01u; // no clock divisor
    PWM_TIMER.CTRLB = 0x13u; // CCA, single slope pwm

    // PWM output (PC0)
    // inverted, disable input sensing
    PWM_PORT.DIRSET = PWM_MASK;
    PWM_PORT.PIN0CTRL = 0x47u;

    // LAT output (PC7)
    // disable input sensing
    // event channel 0 as output value
    LAT_PORT.DIRSET = LAT_MASK;
    LAT_PORT.PIN7CTRL = 0x07u;
    PORTCFG.CLKEVOUT = 0x10u;
    PORTCFG.EVOUTSEL = 0x00u;

    // line meta data input
    META_PORT.DIRCLR = 0xffu;
}

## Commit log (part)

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2019-08-24 driver board layout progress
2019-08-25 add xmega source code
2019-08-25 implement xmega matrix scanning
2019-08-25 remove hex file from git
2019-08-25 add *.hex to .gitignore
2019-08-25 enable pwm output
2019-08-25 board layout progress
2019-08-26 remved unused headers
2019-08-30 add EAGLE scratch files to .gitignore
2019-08-31 finalizing board layout
2019-08-31 add reset button and status leds
2019-09-01 start implementing avr board support
2019-09-01 fix pinout for rpi header
2019-09-01 update pin mapping
2019-09-01 implementing frame header
2019-09-01 adjust xmega crc computation
2019-09-17 adjust spacing of 16-pin headers
2019-09-18 implement data mux pins
2019-09-18 add pull ups for register and buffer output enable lines
2019-09-18 cleanup avr code organization
2019-09-18 more spacing between panel headers
2019-09-18 implement avr vsync muxing
2019-09-18 implement avr external SRAM read command
2019-09-18 implement avr initSRAM()
2019-09-19 fix SRAM pin assignments
2019-09-19 consolidate duplicate signals on board
2019-09-19 fix avr build issues
2019-09-19 cleanup names for avr vsync constants
2019-09-25 enable avr config loading from DPI
2019-09-25 blink led 1 while waiting for config
2019-09-25 use sram bank 1 for config loading
2019-09-25 adjust DPI timing
2019-09-25 debugging vsync wait when loading config
2019-09-25 dedicated vsync input pin
2019-09-25 fix sram chip select pins
2019-09-25 debugging vsync timing when loading config
2019-09-27 additional pull-up resistors
2019-09-27 blink config led
2019-09-27 debugging
2019-09-28 fix sram init
2019-09-28 debugging config
2019-12-19 update boot config
2019-12-19 new output format
2019-12-19 use SDL for DPI output
2019-12-19 documentation for panel muxing
2019-12-19 implement udp support for new driver
2020-01-08 new driver board
2020-01-08 update code to match new driver board
2020-01-08 update rpi boot config for new driver board
2020-01-10 avr dma tweak
2020-01-10 use avr isr instead of dma
2020-02-01 debugging avr timing
2020-02-02 move back to raw framebuffer
2020-02-02 fix dpi RGB order
2020-02-02 adjust scan header offset
2020-02-02 two bytes for pwm
2020-02-02 two bytes for pulse width
2020-02-02 debugging timing
2020-02-02 invert pixel clock
2020-02-02 RGB order
2020-02-02 code cleanup
2020-02-02 debugging prints
2020-02-02 more forgiveness when capturing row meta
2020-02-02 fix row encoding
2020-02-02 fix panel rgb
2020-02-02 fix panel pwm
2020-02-03 invert latch signal
2020-02-06 adjust dpi settings
2020-02-06 test patterns
2020-02-06 force gpio mode
2020-02-06 debugging row select
2020-02-06 simplify isr code
2020-02-07 row select non-inverted
2020-02-07 disable test pattern
2020-02-08 enable test pattern
2020-02-08 support for sn5266 chips
2020-02-08 qiangli Q3E panel
2020-02-18 hub75 panel
2020-02-18 1600 x 128 array
2020-02-18 update rpi config for latest ubuntu image
2020-02-25 debugging qiangli panel
2020-02-25 fix compiler warnings
2020-02-25 qiangli dpi config
2020-02-25 bug fix
2020-02-25 fix pwm bits
2020-02-25 fix segfault
2020-02-25 cleanup old files
2020-02-25 display ethernet address
2020-02-25 remove debug print
2020-02-25 adjust systemd unit file
2020-02-25 test vsync
2020-02-26 remove vestigial vsync from avr code
2020-02-26 new board layout with shorter traces
2020-02-26 board layout tweak
2020-02-27 update xmega code for new board
2020-02-27 update MatrixDriver to match new board
2020-02-27 dynamically allocate frame packet buffer
2020-02-27 more verbose logging
2020-03-06 add pixel mapping class (enables more flexibility with panel arrangement)
2020-03-06 implement panel remapping
2020-06-13 change panel configuration
2020-06-13 fix issues with new board layout
2020-06-17 add RemapInterleaved32A class to support panels with row interleaving
2020-06-17 add HUB75R mode for 8-bit row addressing
2020-06-17 add functions for estimating dimensions of remapped canvas
2020-06-17 fix bug when estimating dimensions of remapped canvas
2020-06-17 fix bug in RemapInterleaved32A
2020-06-19 added HUB75AB 2-bit row select address
2020-06-20 fix white-space inconsistencies (no functional change)
2020-06-20 add RemapInterleavedZ16AB class
2020-06-20 add RemapInterleavedZ8AB class
2020-06-20 cleanup handling on interleaving support. interleaving mode is now a constructor argument and is handled as a separate layer of coordinate translation.
2020-06-20 add more comments
2020-06-20 change interleaving dim function argument names for clarity
2020-06-20 fixed offset bug of Z08AB and Z16AB Interleaving
2020-06-21 implementing Transformers
2020-06-22 implemented mirrorh mirrorv for Z32ABC
2020-06-22 name changes
2020-06-25 reduce glitching caused by external updates to frame buffer
2020-06-25 create utility for generating test patterns
2020-06-25 change color mapping to CIE 1931 for production purposes.
2020-06-25 fix bug in PWM striping
2020-06-26 fix hang when NTP adjusts system clock
2020-06-30 Create LICENSE
